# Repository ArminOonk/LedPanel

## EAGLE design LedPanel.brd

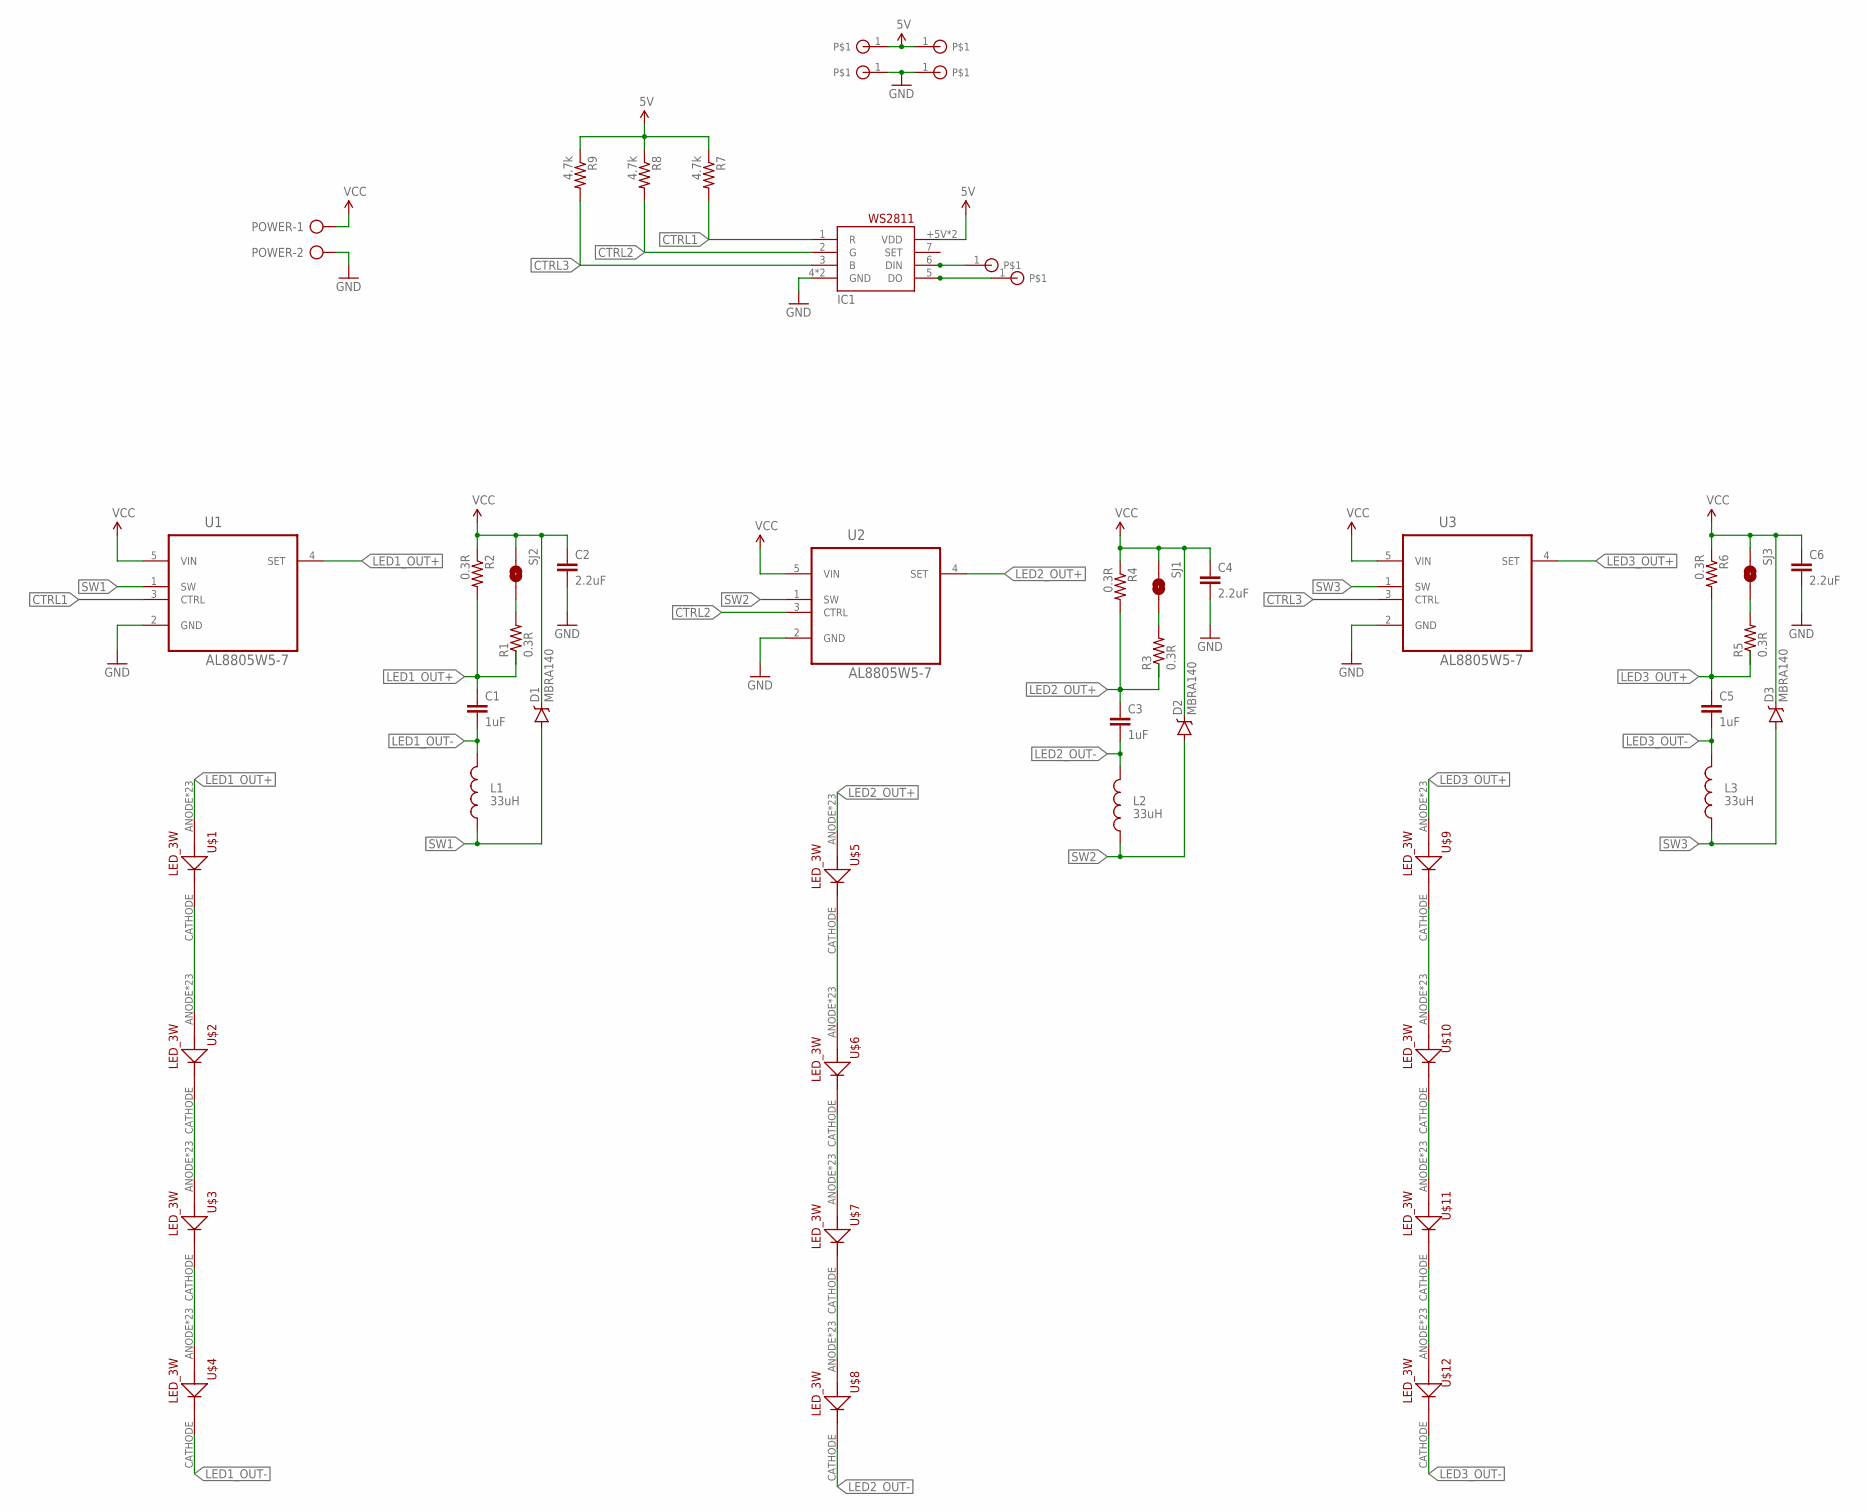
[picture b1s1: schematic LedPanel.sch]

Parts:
5V: 5V; SOLDER_PAD
C1, C3, C5: 1uF; 1206-CAP
C2, C4, C6: 2.2uF; 1206-CAP
D1, D2, D3: MBRA140; SMA-DIODE
DI: DI; SOLDER_PAD
DO: DO; SOLDER_PAD
IC1: WS2811-SOP8; SO08-SKINNYPADS
L1, L2, L3: 33uH; SRN6045
POWER: AK500/2
R1, R2, R3, R4, R5, R6: 0.3R; 0805
R7, R8, R9: 4.7k; 0805
SJ1, SJ2, SJ3: NO Jumper; PAD-JUMPER-2-NO_NO_SILK
U1, U2, U3: AL8805W5-7; SOT95P280X130-5N
U$1, U$2, U$3, U$4, U$5, U$6, U$7, U$8, U$9, U$10, U$11, U$12: LED_3W
U$15, U$18: GND; SOLDER_PAD
U$16: 5V; SOLDER_PAD

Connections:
5V: 5V.1, IC1.8 (VDD), IC1.+5V (VDD), R7.1, R8.1, R9.1, U$16.1
CTRL1: IC1.1 (R), R7.2, U1.3 (CTRL)
CTRL2: IC1.2 (G), R8.2, U2.3 (CTRL)
CTRL3: IC1.3 (B), R9.2, U3.3 (CTRL)
GND: C2.2, C4.2, C6.2, IC1.4 (GND), IC1.GND, POWER.2, U1.2 (GND), U2.2 (GND), U3.2 (GND), U$15.1, U$18.1
LED1_OUT+: C1.1, R1.1, R2.2, U1.4 (SET), U$1.ANODE, U$1.P$1 (ANODE), U$1.P$2 (ANODE), U$1.P$3 (ANODE), U$1.P$4 (ANODE), U$1.P$5 (ANODE), U$1.P$6 (ANODE), U$1.P$7 (ANODE), U$1.P$8 (ANODE), U$1.P$9 (ANODE), U$1.P$10 (ANODE), U$1.P$11 (ANODE), U$1.P$12 (ANODE), U$1.P$13 (ANODE), U$1.P$14 (ANODE), U$1.P$15 (ANODE), U$1.P$16 (ANODE), U$1.P$17 (ANODE), U$1.P$18 (ANODE), U$1.P$19 (ANODE), U$1.P$20 (ANODE), U$1.P$21 (ANODE), U$1.SLUG (ANODE)
LED1_OUT-: C1.2, L1.2, U$4.CATHODE
LED2_OUT+: C3.1, R3.1, R4.2, U2.4 (SET), U$5.ANODE, U$5.P$1 (ANODE), U$5.P$2 (ANODE), U$5.P$3 (ANODE), U$5.P$4 (ANODE), U$5.P$5 (ANODE), U$5.P$6 (ANODE), U$5.P$7 (ANODE), U$5.P$8 (ANODE), U$5.P$9 (ANODE), U$5.P$10 (ANODE), U$5.P$11 (ANODE), U$5.P$12 (ANODE), U$5.P$13 (ANODE), U$5.P$14 (ANODE), U$5.P$15 (ANODE), U$5.P$16 (ANODE), U$5.P$17 (ANODE), U$5.P$18 (ANODE), U$5.P$19 (ANODE), U$5.P$20 (ANODE), U$5.P$21 (ANODE), U$5.SLUG (ANODE)
LED2_OUT-: C3.2, L2.2, U$8.CATHODE
LED3_OUT+: C5.1, R5.1, R6.2, U3.4 (SET), U$9.ANODE, U$9.P$1 (ANODE), U$9.P$2 (ANODE), U$9.P$3 (ANODE), U$9.P$4 (ANODE), U$9.P$5 (ANODE), U$9.P$6 (ANODE), U$9.P$7 (ANODE), U$9.P$8 (ANODE), U$9.P$9 (ANODE), U$9.P$10 (ANODE), U$9.P$11 (ANODE), U$9.P$12 (ANODE), U$9.P$13 (ANODE), U$9.P$14 (ANODE), U$9.P$15 (ANODE), U$9.P$16 (ANODE), U$9.P$17 (ANODE), U$9.P$18 (ANODE), U$9.P$19 (ANODE), U$9.P$20 (ANODE), U$9.P$21 (ANODE), U$9.SLUG (ANODE)
LED3_OUT-: C5.2, L3.2, U$12.CATHODE
unnamed: U$3.CATHODE, U$4.ANODE, U$4.P$1 (ANODE), U$4.P$2 (ANODE), U$4.P$3 (ANODE), U$4.P$4 (ANODE), U$4.P$5 (ANODE), U$4.P$6 (ANODE), U$4.P$7 (ANODE), U$4.P$8 (ANODE), U$4.P$9 (ANODE), U$4.P$10 (ANODE), U$4.P$11 (ANODE), U$4.P$12 (ANODE), U$4.P$13 (ANODE), U$4.P$14 (ANODE), U$4.P$15 (ANODE), U$4.P$16 (ANODE), U$4.P$17 (ANODE), U$4.P$18 (ANODE), U$4.P$19 (ANODE), U$4.P$20 (ANODE), U$4.P$21 (ANODE), U$4.SLUG (ANODE)
unnamed: U$2.CATHODE, U$3.ANODE, U$3.P$1 (ANODE), U$3.P$2 (ANODE), U$3.P$3 (ANODE), U$3.P$4 (ANODE), U$3.P$5 (ANODE), U$3.P$6 (ANODE), U$3.P$7 (ANODE), U$3.P$8 (ANODE), U$3.P$9 (ANODE), U$3.P$10 (ANODE), U$3.P$11 (ANODE), U$3.P$12 (ANODE), U$3.P$13 (ANODE), U$3.P$14 (ANODE), U$3.P$15 (ANODE), U$3.P$16 (ANODE), U$3.P$17 (ANODE), U$3.P$18 (ANODE), U$3.P$19 (ANODE), U$3.P$20 (ANODE), U$3.P$21 (ANODE), U$3.SLUG (ANODE)
unnamed: U$1.CATHODE, U$2.ANODE, U$2.P$1 (ANODE), U$2.P$2 (ANODE), U$2.P$3 (ANODE), U$2.P$4 (ANODE), U$2.P$5 (ANODE), U$2.P$6 (ANODE), U$2.P$7 (ANODE), U$2.P$8 (ANODE), U$2.P$9 (ANODE), U$2.P$10 (ANODE), U$2.P$11 (ANODE), U$2.P$12 (ANODE), U$2.P$13 (ANODE), U$2.P$14 (ANODE), U$2.P$15 (ANODE), U$2.P$16 (ANODE), U$2.P$17 (ANODE), U$2.P$18 (ANODE), U$2.P$19 (ANODE), U$2.P$20 (ANODE), U$2.P$21 (ANODE), U$2.SLUG (ANODE)
unnamed: U$7.CATHODE, U$8.ANODE, U$8.P$1 (ANODE), U$8.P$2 (ANODE), U$8.P$3 (ANODE), U$8.P$4 (ANODE), U$8.P$5 (ANODE), U$8.P$6 (ANODE), U$8.P$7 (ANODE), U$8.P$8 (ANODE), U$8.P$9 (ANODE), U$8.P$10 (ANODE), U$8.P$11 (ANODE), U$8.P$12 (ANODE), U$8.P$13 (ANODE), U$8.P$14 (ANODE), U$8.P$15 (ANODE), U$8.P$16 (ANODE), U$8.P$17 (ANODE), U$8.P$18 (ANODE), U$8.P$19 (ANODE), U$8.P$20 (ANODE), U$8.P$21 (ANODE), U$8.SLUG (ANODE)
unnamed: U$6.CATHODE, U$7.ANODE, U$7.P$1 (ANODE), U$7.P$2 (ANODE), U$7.P$3 (ANODE), U$7.P$4 (ANODE), U$7.P$5 (ANODE), U$7.P$6 (ANODE), U$7.P$7 (ANODE), U$7.P$8 (ANODE), U$7.P$9 (ANODE), U$7.P$10 (ANODE), U$7.P$11 (ANODE), U$7.P$12 (ANODE), U$7.P$13 (ANODE), U$7.P$14 (ANODE), U$7.P$15 (ANODE), U$7.P$16 (ANODE), U$7.P$17 (ANODE), U$7.P$18 (ANODE), U$7.P$19 (ANODE), U$7.P$20 (ANODE), U$7.P$21 (ANODE), U$7.SLUG (ANODE)
unnamed: R1.2, SJ2.2
unnamed: U$5.CATHODE, U$6.ANODE, U$6.P$1 (ANODE), U$6.P$2 (ANODE), U$6.P$3 (ANODE), U$6.P$4 (ANODE), U$6.P$5 (ANODE), U$6.P$6 (ANODE), U$6.P$7 (ANODE), U$6.P$8 (ANODE), U$6.P$9 (ANODE), U$6.P$10 (ANODE), U$6.P$11 (ANODE), U$6.P$12 (ANODE), U$6.P$13 (ANODE), U$6.P$14 (ANODE), U$6.P$15 (ANODE), U$6.P$16 (ANODE), U$6.P$17 (ANODE), U$6.P$18 (ANODE), U$6.P$19 (ANODE), U$6.P$20 (ANODE), U$6.P$21 (ANODE), U$6.SLUG (ANODE)
unnamed: R3.2, SJ1.2
unnamed: U$11.CATHODE, U$12.ANODE, U$12.P$1 (ANODE), U$12.P$2 (ANODE), U$12.P$3 (ANODE), U$12.P$4 (ANODE), U$12.P$5 (ANODE), U$12.P$6 (ANODE), U$12.P$7 (ANODE), U$12.P$8 (ANODE), U$12.P$9 (ANODE), U$12.P$10 (ANODE), U$12.P$11 (ANODE), U$12.P$12 (ANODE), U$12.P$13 (ANODE), U$12.P$14 (ANODE), U$12.P$15 (ANODE), U$12.P$16 (ANODE), U$12.P$17 (ANODE), U$12.P$18 (ANODE), U$12.P$19 (ANODE), U$12.P$20 (ANODE), U$12.P$21 (ANODE), U$12.SLUG (ANODE)
unnamed: U$10.CATHODE, U$11.ANODE, U$11.P$1 (ANODE), U$11.P$2 (ANODE), U$11.P$3 (ANODE), U$11.P$4 (ANODE), U$11.P$5 (ANODE), U$11.P$6 (ANODE), U$11.P$7 (ANODE), U$11.P$8 (ANODE), U$11.P$9 (ANODE), U$11.P$10 (ANODE), U$11.P$11 (ANODE), U$11.P$12 (ANODE), U$11.P$13 (ANODE), U$11.P$14 (ANODE), U$11.P$15 (ANODE), U$11.P$16 (ANODE), U$11.P$17 (ANODE), U$11.P$18 (ANODE), U$11.P$19 (ANODE), U$11.P$20 (ANODE), U$11.P$21 (ANODE), U$11.SLUG (ANODE)
unnamed: U$9.CATHODE, U$10.ANODE, U$10.P$1 (ANODE), U$10.P$2 (ANODE), U$10.P$3 (ANODE), U$10.P$4 (ANODE), U$10.P$5 (ANODE), U$10.P$6 (ANODE), U$10.P$7 (ANODE), U$10.P$8 (ANODE), U$10.P$9 (ANODE), U$10.P$10 (ANODE), U$10.P$11 (ANODE), U$10.P$12 (ANODE), U$10.P$13 (ANODE), U$10.P$14 (ANODE), U$10.P$15 (ANODE), U$10.P$16 (ANODE), U$10.P$17 (ANODE), U$10.P$18 (ANODE), U$10.P$19 (ANODE), U$10.P$20 (ANODE), U$10.P$21 (ANODE), U$10.SLUG (ANODE)
unnamed: R5.2, SJ3.2
unnamed: DI.1, IC1.6 (DIN)
unnamed: DO.1, IC1.5 (DO)
SW1: D1.A, L1.1, U1.1 (SW)
SW2: D2.A, L2.1, U2.1 (SW)
SW3: D3.A, L3.1, U3.1 (SW)
VCC: C2.1, C4.1, C6.1, D1.C, D2.C, D3.C, POWER.1, R2.1, R4.1, R6.1, SJ1.1, SJ2.1, SJ3.1, U1.5 (VIN), U2.5 (VIN), U3.5 (VIN)

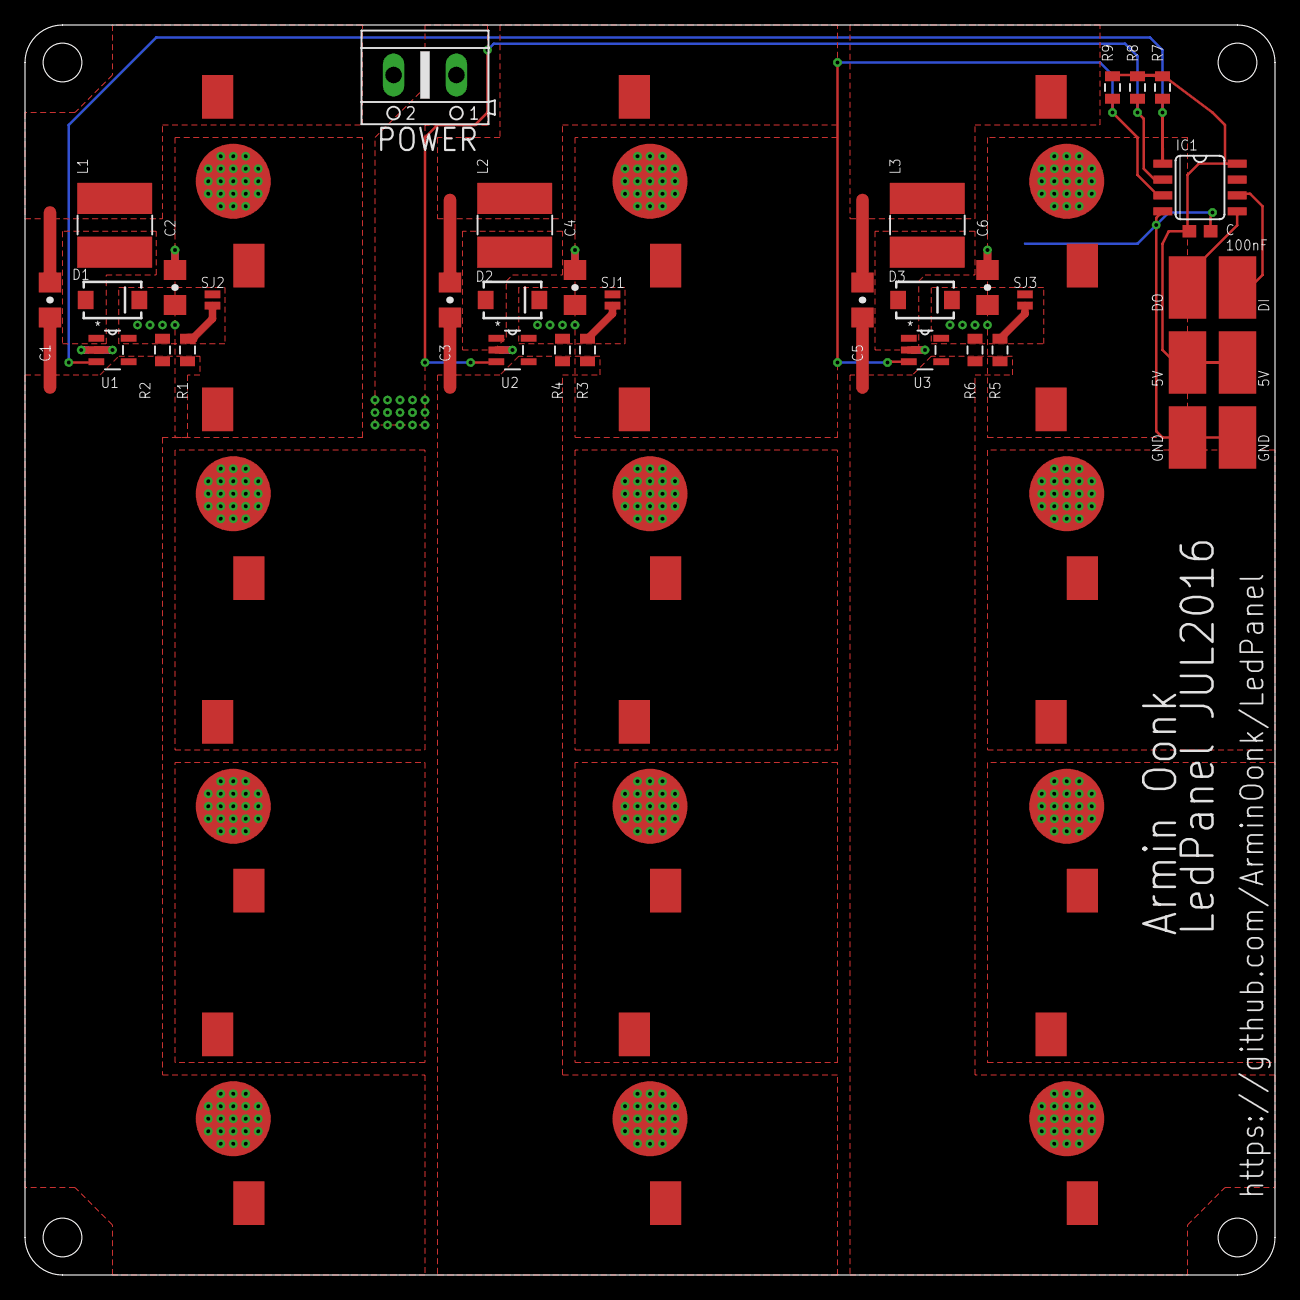
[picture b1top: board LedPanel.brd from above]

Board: 2 copper layers, 100.0 x 100.0 mm, 47 parts (0 on the bottom side), 29 nets.

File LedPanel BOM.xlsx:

| Part | Value | Device | Description | OC_FARNELL | Aliexpress
 | C1 | 1uF | 1.0UF50V10%(1206) | CAP-09822 |  | http://www.aliexpress.com/item/Free-Shipping-Chip-capacitor-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
 | C2 | 2.2uF | 2.2UF50V10%(1206) | CAP-10009 |  | http://www.aliexpress.com/item/SMD-Capacitor-1206-2-2UF-50V-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
 | C3 | 1uF | 1.0UF50V10%(1206) | CAP-09822 |  | http://www.aliexpress.com/item/Free-Shipping-Chip-capacitor-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
 | C4 | 2.2uF | 2.2UF50V10%(1206) | CAP-10009 |  | http://www.aliexpress.com/item/SMD-Capacitor-1206-2-2UF-50V-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
 | C5 | 1uF | 1.0UF50V10%(1206) | CAP-09822 |  | http://www.aliexpress.com/item/Free-Shipping-Chip-capacitor-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
 | C6 | 2.2uF | 2.2UF50V10%(1206) | CAP-10009 |  | http://www.aliexpress.com/item/SMD-Capacitor-1206-2-2UF-50V-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
 | D1 | MBRA140 | DIODE-SCHOTTKY-MBRA140 | Schottky diodes in SFE's production catalog |  | http://www.aliexpress.com/item/20PCS-MBRA140-MBRA140T3G/3245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
 | D2 | MBRA140 | DIODE-SCHOTTKY-MBRA140 | Schottky diodes in SFE's production catalog |  | http://www.aliexpress.com/item/20PCS-MBRA140-MBRA140T3G/3245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
 | D3 | MBRA140 | DIODE-SCHOTTKY-MBRA140 | Schottky diodes in SFE's production catalog |  | http://www.aliexpress.com/item/20PCS-MBRA140-MBRA140T3G/3245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
 | IC1 | WS2811-SOP8 | WS2811-SOP8 |  |  | http://www.aliexpress.com/item/Free-Shipping-100pcs-lot-WS28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
 | L1 | 33uH | INDUCTORBOURNS_SRN6045 | Inductors | 2061655
 | L2 | 33uH | INDUCTORBOURNS_SRN6045 | Inductors | 2061655
 | L3 | 33uH | INDUCTORBOURNS_SRN6045 | Inductors | 2061655
 | POWER |  | AK500/2 | CONNECTOR |  | http://www.aliexpress.com/item/Wholesale-Price-20Pcs-2-Pole-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
 | R1 | 0.3R | 0.3OHM-1/8W-1%(0805) | RES-11622 |  | http://www.aliexpress.com/item/0805-SMD-Resistor-1-0-3-ohm-5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
 | R2 | 0.3R | 0.3OHM-1/8W-1%(0805) | RES-11622 |  | http://www.aliexpress.com/item/0805-SMD-Resistor-1-0-3-ohm-5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
 | R3 | 0.3R | 0.3OHM-1/8W-1%(0805) | RES-11622 |  | http://www.aliexpress.com/item/0805-SMD-Resistor-1-0-3-ohm-5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
 | R4 | 0.3R | 0.3OHM-1/8W-1%(0805) | RES-11622 |  | http://www.aliexpress.com/item/0805-SMD-Resistor-1-0-3-ohm-5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
 | R5 | 0.3R | 0.3OHM-1/8W-1%(0805) | RES-11622 |  | http://www.aliexpress.com/item/0805-SMD-Resistor-1-0-3-ohm-5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
 | R6 | 0.3R | 0.3OHM-1/8W-1%(0805) | RES-11622 |  | http://www.aliexpress.com/item/0805-SMD-Resistor-1-0-3-ohm-5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
 | R7 | 4.7k | 0.3OHM-1/8W-1%(0805) | RES-11622 |  | http://www.aliexpress.com/item/100pcs-lot-SMD-Chip-Resistor-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
 | R8 | 4.7k | 0.3OHM-1/8W-1%(0805) | RES-11622 |  | http://www.aliexpress.com/item/100pcs-lot-SMD-Chip-Resistor-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
 | R9 | 4.7k | 0.3OHM-1/8W-1%(0805) | RES-11622 |  | http://www.aliexpress.com/item/100pcs-lot-SMD-Chip-Resistor-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
 | U1 | AL8805W5-7 | AL8805W5-7 | HIGH EFFICIENCY 30V 1A BUCK LED DRIVER | 1904023 | http://www.aliexpress.com/item/Freeshipping-AL8805-AL8805W5-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
 | U2 | AL8805W5-7 | AL8805W5-7 | HIGH EFFICIENCY 30V 1A BUCK LED DRIVER | 1904023 | http://www.aliexpress.com/item/Freeshipping-AL8805-AL8805W5-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
 | U3 | AL8805W5-7 | AL8805W5-7 | HIGH EFFICIENCY 30V 1A BUCK LED DRIVER | 1904023 | http://www.aliexpress.com/item/Freeshipping-AL8805-AL8805W5-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
 | 3W led, choose your own color
 | U$1 | LED_3W | LED_3W | 3W Led footprint optimized for heat disipation
 | U$2 | LED_3W | LED_3W | 3W Led footprint optimized for heat disipation
 | U$3 | LED_3W | LED_3W | 3W Led footprint optimized for heat disipation
 | U$4 | LED_3W | LED_3W | 3W Led footprint optimized for heat disipation
 | U$5 | LED_3W | LED_3W | 3W Led footprint optimized for heat disipation
 | U$6 | LED_3W | LED_3W | 3W Led footprint optimized for heat disipation
 | U$7 | LED_3W | LED_3W | 3W Led footprint optimized for heat disipation
 | U$8 | LED_3W | LED_3W | 3W Led footprint optimized for heat disipation
 | U$9 | LED_3W | LED_3W | 3W Led footprint optimized for heat disipation
 | U$10 | LED_3W | LED_3W | 3W Led footprint optimized for heat disipation
 | U$11 | LED_3W | LED_3W | 3W Led footprint optimized for heat disipation
 | U$12 | LED_3W | LED_3W | 3W Led footprint optimized for heat disipation
 | Not part
 | SJ1 | NO Jumper | JUMPER-PAD-2-NO
 | SJ2 | NO Jumper | JUMPER-PAD-2-NO
 | SJ3 | NO Jumper | JUMPER-PAD-2-NO
 | U$15 | GND | SOLDER_PAD
 | U$16 | 5V | SOLDER_PAD
 | U$18 | GND | SOLDER_PAD
 | 5V | 5V | SOLDER_PAD
 | DI | DI | SOLDER_PAD
 | DO | DO | SOLDER_PAD

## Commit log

2016-06-29 Starting with the led driver
2016-06-29 Connecting the led driver, fixing some issues
2016-07-02 Creating 3 string of 4 leds. 12 3W leds in total. Peak power is 36W?
2016-07-05 Adding ws8211 to control the leds
2016-07-05 Layout first led driver
2016-07-05 Added more inspiration files
2016-07-06 Testing username storage, nothing important
2016-07-06 Routing everything
2016-07-06 100% routed
2016-07-06 Cooling copper
2016-07-07 Tweaking silkscreen, generated BOM
2016-07-11 Added suppliers
2016-07-11 Creating V1

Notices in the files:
parts and their libraries:
SparkFun-Resistors: Licensing: CC v3.0 Share-Alike You are welcome to use this library for commercial purposes.
